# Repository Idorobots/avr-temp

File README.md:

# avr-temp
A minimal, AVR based digital thermometer using DS18B20 & a triple 7-segment display.

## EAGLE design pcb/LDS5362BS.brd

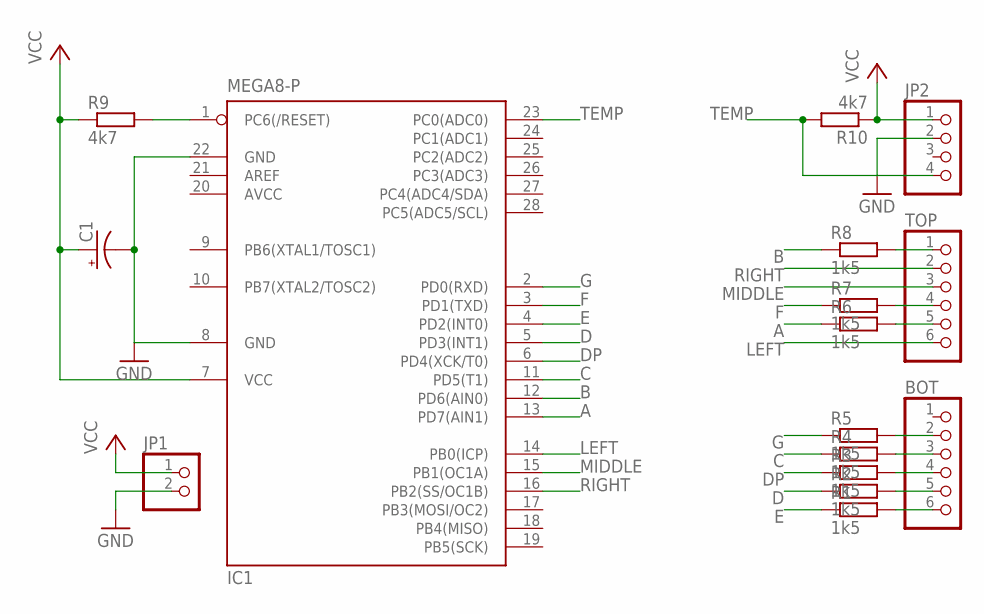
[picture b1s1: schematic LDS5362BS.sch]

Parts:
BOT: PINHD-1X6; 1X06
C1: CPOL-US153CLV-0505; 153CLV-0505
IC1: MEGA8-P; DIL28-3
JP1: PINHD-1X2; 1X02
JP2: PINHD-1X4; 1X04
R1, R2, R3, R4, R5, R6, R7, R8: 1k5; R1206
R9, R10: 4k7; R1206
TOP: PINHD-1X6; 1X06

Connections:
A: IC1.13 (PD7(AIN1)), R6.1
AVCC: IC1.20 (AVCC)
B: IC1.12 (PD6(AIN0)), R8.1
C: IC1.11 (PD5(T1)), R4.1
D: IC1.5 (PD3(INT1)), R2.1
DP: IC1.6 (PD4(XCK/T0)), R3.1
E: IC1.4 (PD2(INT0)), R1.1
F: IC1.3 (PD1(TXD)), R7.1
G: IC1.2 (PD0(RXD)), R5.1
GND: C1.-, IC1.8 (GND), IC1.22 (GND), JP1.2, JP2.2
LEFT: IC1.14 (PB0(ICP)), TOP.6
MIDDLE: IC1.15 (PB1(OC1A)), TOP.3
unnamed: R8.2, TOP.1
unnamed: R7.2, TOP.4
unnamed: R6.2, TOP.5
unnamed: BOT.2, R5.2
unnamed: BOT.3, R4.2
unnamed: BOT.4, R3.2
unnamed: BOT.5, R2.2
unnamed: BOT.6, R1.2
unnamed: IC1.1 (PC6(/RESET)), R9.2
RIGHT: IC1.16 (PB2(SS/OC1B)), TOP.2
TEMP: IC1.23 (PC0(ADC0)), JP2.4, R10.2
VCC: C1.+, IC1.7 (VCC), JP1.1, JP2.1, R9.1, R10.1

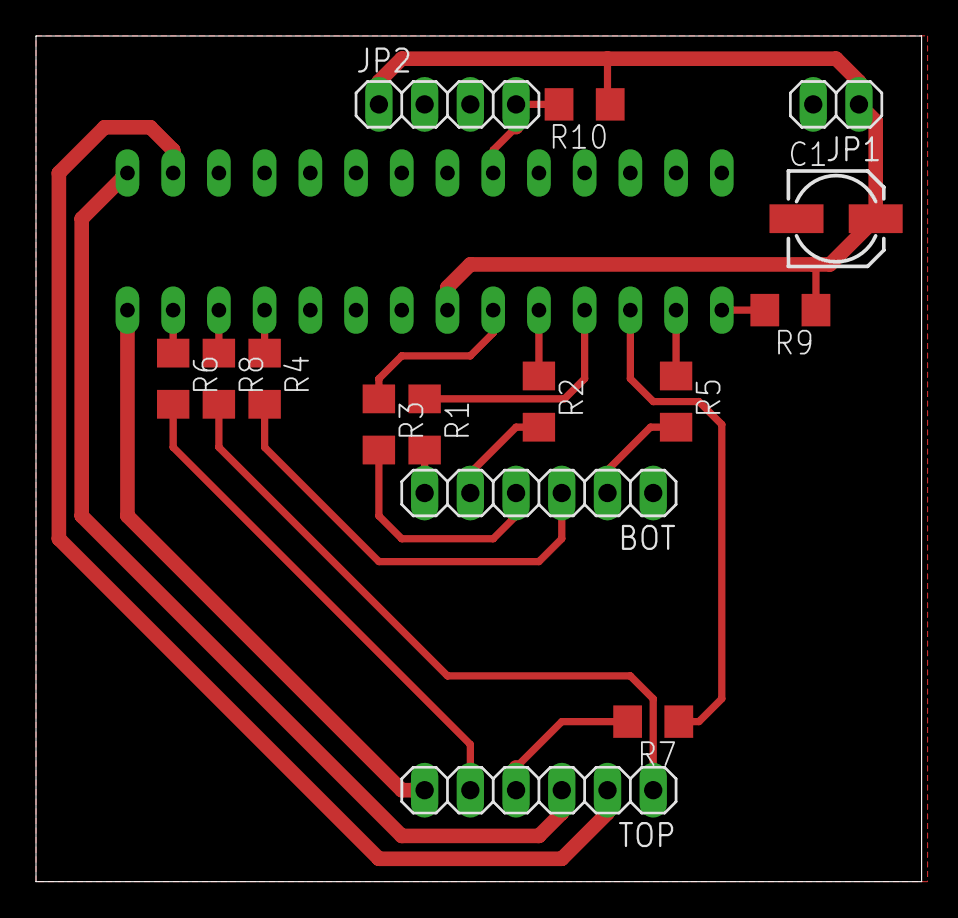
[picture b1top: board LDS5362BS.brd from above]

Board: 2 copper layers, 49.2 x 47.0 mm, 16 parts (1 on the bottom side), 23 nets.

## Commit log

2015-01-02 Fixed LSD5361BS control port overwriting more pins than needed.
2015-01-03 LSD5361BS has fixed number of segments.
2015-01-04 Hurr durr...
2015-01-04 Added Eagle project file.
2015-01-04 Added display schematic & board stubs.
2015-01-05 Fixed board dimentions & added GND plane.
2015-04-01 Updated the schematic with ATmega8 & passives.
2015-04-01 Routed the PCB.
2015-04-01 Renamed files appropriately.
2015-04-02 Created a README.
2015-06-22 Removed Eagle project file.
2015-08-08 Added programmable measurement delay.
2015-08-08 Added Makefile rules and fusebit configuration suitable for TL866.
